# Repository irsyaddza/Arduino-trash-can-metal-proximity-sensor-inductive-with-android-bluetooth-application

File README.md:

# 🤖 Arduino-trash-can-metal-proximity-sensor-inductive-with-android-bluetooth-application

## 📋 Overview

This project implements an automated metal detection system using Arduino. When metal is detected, a servo motor activates and a counter increments. The system features a digital display to show the count, LED indicators, and Bluetooth connectivity for remote control and monitoring.

## ✨ Features

- **Real-time Metal Detection**: Automatically detects when metal objects come near the proximity sensor
- **Servo Activation**: Servo motor automatically opens and closes when metal is detected
- **Digital Counter**: TM1637 display shows the number of metal objects detected
- **LED Indicators**: Visual indications for metal detection and servo status
- **Bluetooth Control**: Remote operation via Bluetooth with commands to:
  - Open the servo
  - Close the servo
  - Reset the counter
- **Serial Monitoring**: Live status updates through the serial monitor

## 🔌 Hardware Requirements

- Arduino board (Uno or similar)
- Proximity Sensor Inductive
- Servo motor
- TM1637 4-digit 7-segment display
- HC-05/HC-06 Bluetooth module
- 2 LEDs (for metal and servo indicators)
- Resistors for LEDs
- Power supply 12V 5A

## 📲 Pin Configuration

| Component | Arduino Pin |
|-----------|-------------|
| Servo Motor | 9 |
| Proximity Sensor | 2 |
| TM1637 Clock | 5 |
| TM1637 Data | 4 |
| Metal Indicator LED | 6 |
| Servo Indicator LED | 7 |
| Bluetooth RX | 10 |
| Bluetooth TX | 11 |

## 📚 Libraries Used

- **Servo.h**: For controlling the servo motor
- **TM1637Display.h**: For interfacing with the 7-segment display
- **SoftwareSerial.h**: For Bluetooth communication

## 📡 Bluetooth Commands

| Command | Action |
|---------|--------|
| '1' | Open the servo |
| '2' | Close the servo |
| 'R' or 'r' | Reset the counter |

## 💻 Installation

1. Connect the hardware components according to the pin configuration
2. Install the required libraries via Arduino Library Manager:
   - Servo
   - TM1637Display
   - SoftwareSerial (included with Arduino IDE)
3. Upload the code to your Arduino board
4. Connect to the Bluetooth module using a terminal app or custom mobile application

## 🚀 How It Works

1. When a metal object is detected by the proximity sensor, the system:
   - Turns on the metal indicator LED
   - Opens the servo (rotates to 90 degrees)
   - Increments the counter on the display
   - Sends status updates via Serial and Bluetooth
   
2. When the metal object is removed:
   - The metal indicator LED turns off
   - The servo closes (returns to 0 degrees)
   - Status updates are sent via Serial and Bluetooth

3. The counter keeps track of the total number of detections since power-on or last reset

## 📱 Mobile Control

You can control the system remotely using any Bluetooth terminal app:

## 🛠️ Customization

The code can be easily modified for various applications:
- Adjust the servo angle by changing the values in the `openServo()` and `closeServo()` functions
- Modify the delay time after metal detection by changing the value in the `delay()` function
- Adjust the display brightness by changing the value in `display.setBrightness()`

## 🔍 Troubleshooting

- **Servo not moving**: Check power supply and servo connections
- **No detection**: Verify proximity sensor wiring and sensitivity
- **Display issues**: Ensure proper connections to CLK and DIO pins
- **Bluetooth not connecting**: Check baud rate settings and module power

## 👨‍💻 Author

irsyaddza - [Github](https://github.com/irsyaddza)

## 🙏 Acknowledgements

- Thanks to all contributors and testers
- Libraries used in this project
- Inspiration for the design

---

⭐️ If you found this project helpful, please give it a star on GitHub! ⭐️

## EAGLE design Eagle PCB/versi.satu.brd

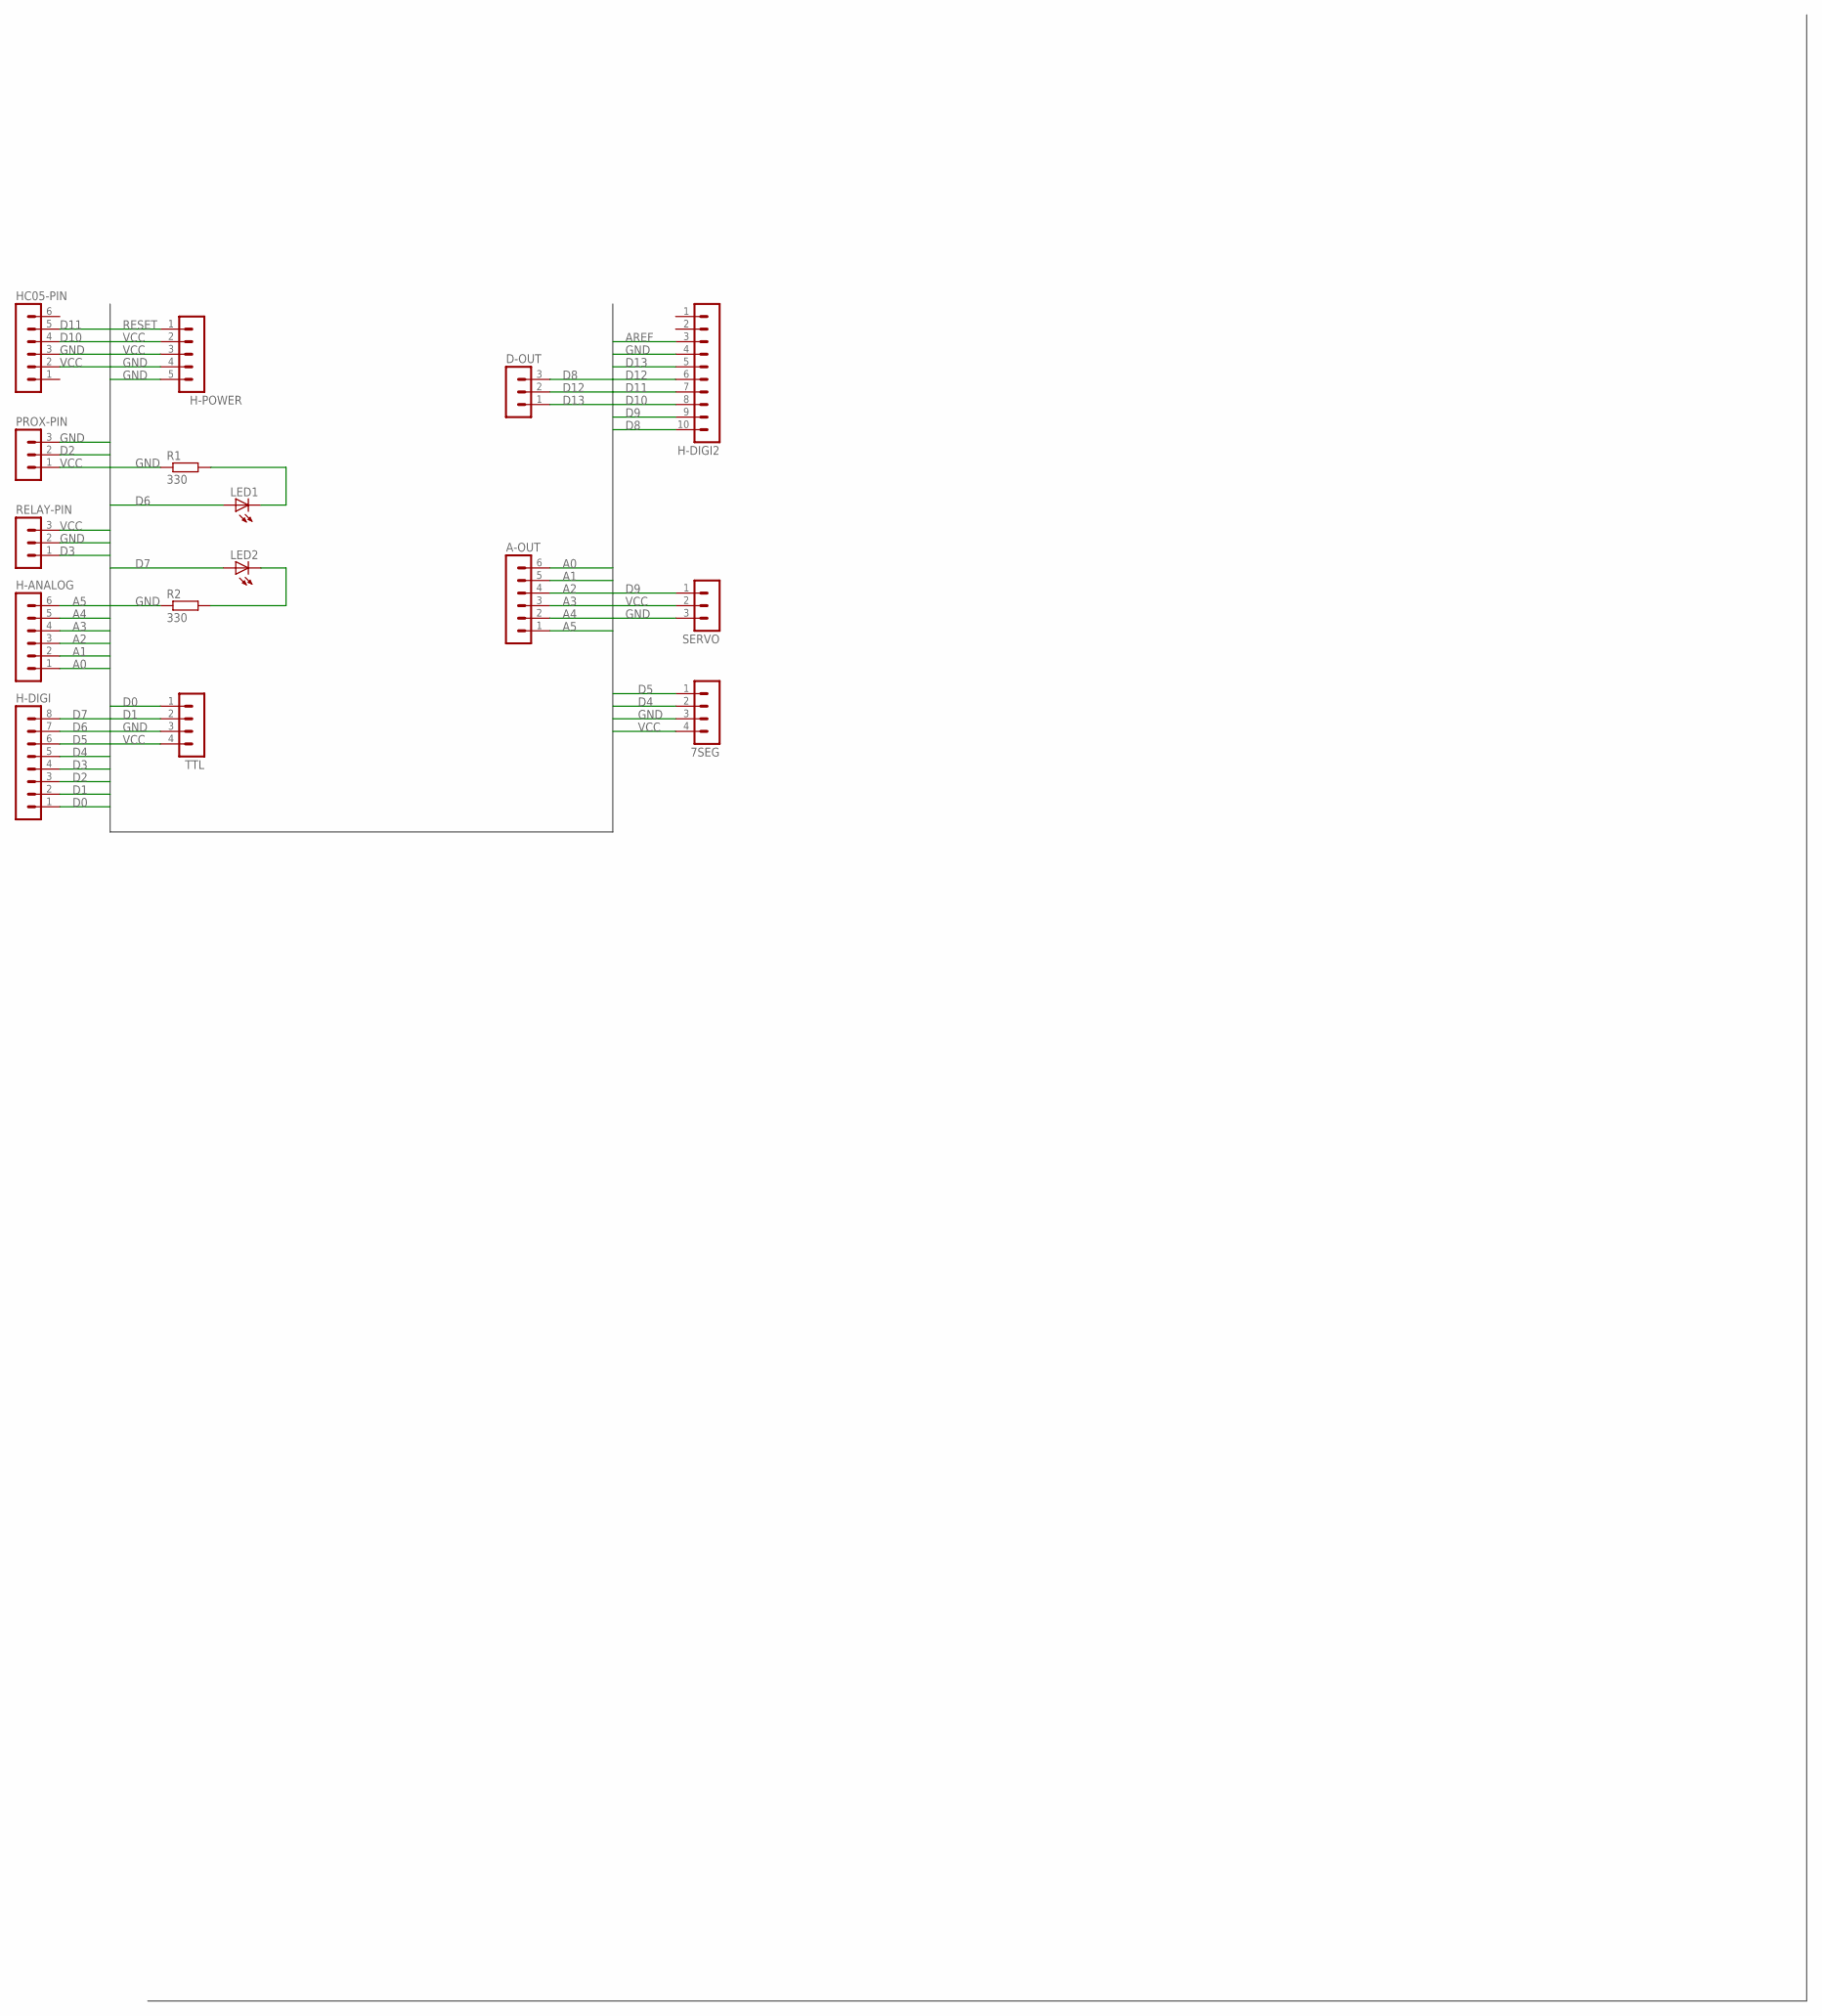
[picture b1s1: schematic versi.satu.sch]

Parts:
7SEG: MA04-1
A-OUT: MA06-1
D-OUT: MA03-1
H-ANALOG: MA06-1
H-DIGI: MA08-1
H-DIGI2: MA10-1
H-POWER: MA05-1
HC05-PIN: MA06-1
LED1, LED2: LED5MM
PROX-PIN: MA03-1
R1, R2: 330; 0207/10
RELAY-PIN: MA03-1
SERVO: MA03-1
TTL: MA04-1

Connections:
A0: A-OUT.6, H-ANALOG.1
A1: A-OUT.5, H-ANALOG.2
A2: A-OUT.4, H-ANALOG.3
A3: A-OUT.3, H-ANALOG.4
A4: A-OUT.2, H-ANALOG.5
A5: A-OUT.1, H-ANALOG.6
AREF: H-DIGI2.3
D0: H-DIGI.1, TTL.1
D1: H-DIGI.2, TTL.2
D2: H-DIGI.3, PROX-PIN.2
D3: H-DIGI.4, RELAY-PIN.1
D4: 7SEG.2, H-DIGI.5
D5: 7SEG.1, H-DIGI.6
D6: H-DIGI.7, LED1.A
D7: H-DIGI.8, LED2.A
D8: D-OUT.3, H-DIGI2.10
D9: H-DIGI2.9, SERVO.1
D10: H-DIGI2.8, HC05-PIN.4
D11: H-DIGI2.7, HC05-PIN.5
D12: D-OUT.2, H-DIGI2.6
D13: D-OUT.1, H-DIGI2.5
GND: 7SEG.3, H-DIGI2.4, H-POWER.4, H-POWER.5, HC05-PIN.3, PROX-PIN.3, R1.1, R2.1, RELAY-PIN.2, SERVO.3, TTL.3
unnamed: LED2.K (C), R2.2
unnamed: LED1.K (C), R1.2
RESET: H-POWER.1
VCC: 7SEG.4, H-POWER.2, H-POWER.3, HC05-PIN.2, PROX-PIN.1, RELAY-PIN.3, SERVO.2, TTL.4

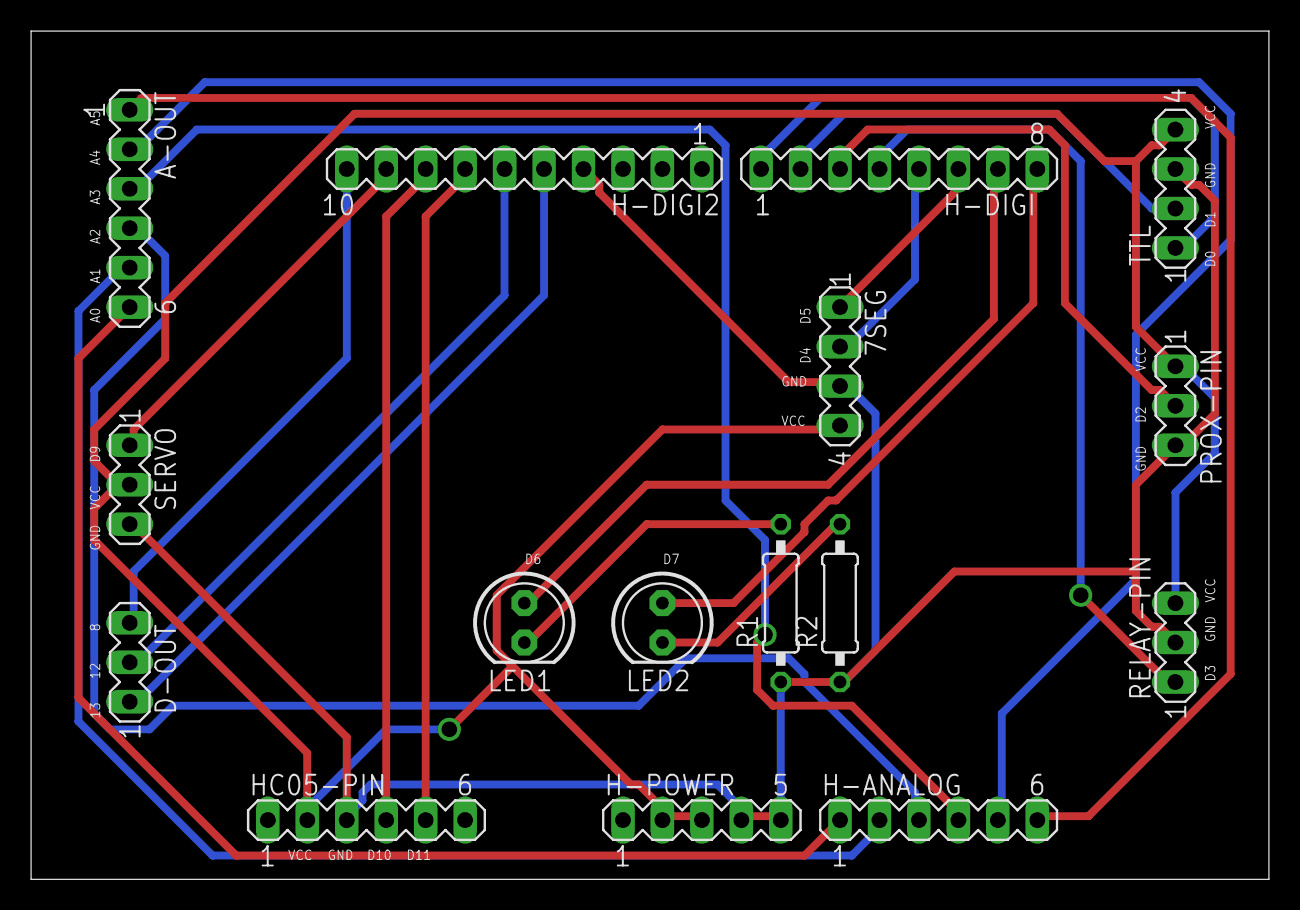
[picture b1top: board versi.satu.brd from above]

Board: 2 copper layers, 79.7 x 54.6 mm, 16 parts (0 on the bottom side), 24 nets.
